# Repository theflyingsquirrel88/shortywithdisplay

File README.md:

# shortywithdisplay
PCB Design for the ShortywithDisplay Project

This Project is based on the design from kripton2035 from eevblog.com
https://www.eevblog.com/forum/testgear/finding-short-on-motherboards-with-a-shorty-(with-display)/

I was fixing my laptop and thinking there is a short somewhere which is hard to pin point. I then came across this project shorty with display and am very imppressed by it. I saw everyone was soldering component onto breadbroad but no PCB was ever designed for this. I then decided to take some time to design a PCB for this so that everyone will have a easier live down the road.
This PCB is designed with KiCAD 9.0. I used mostly 0603 SMD with some through hold components. You may Thesewant to take a look at the original Project to get an idea of what this PCB is for.

These days, you can order PCB online for a really low price. This make DIY project much easier.

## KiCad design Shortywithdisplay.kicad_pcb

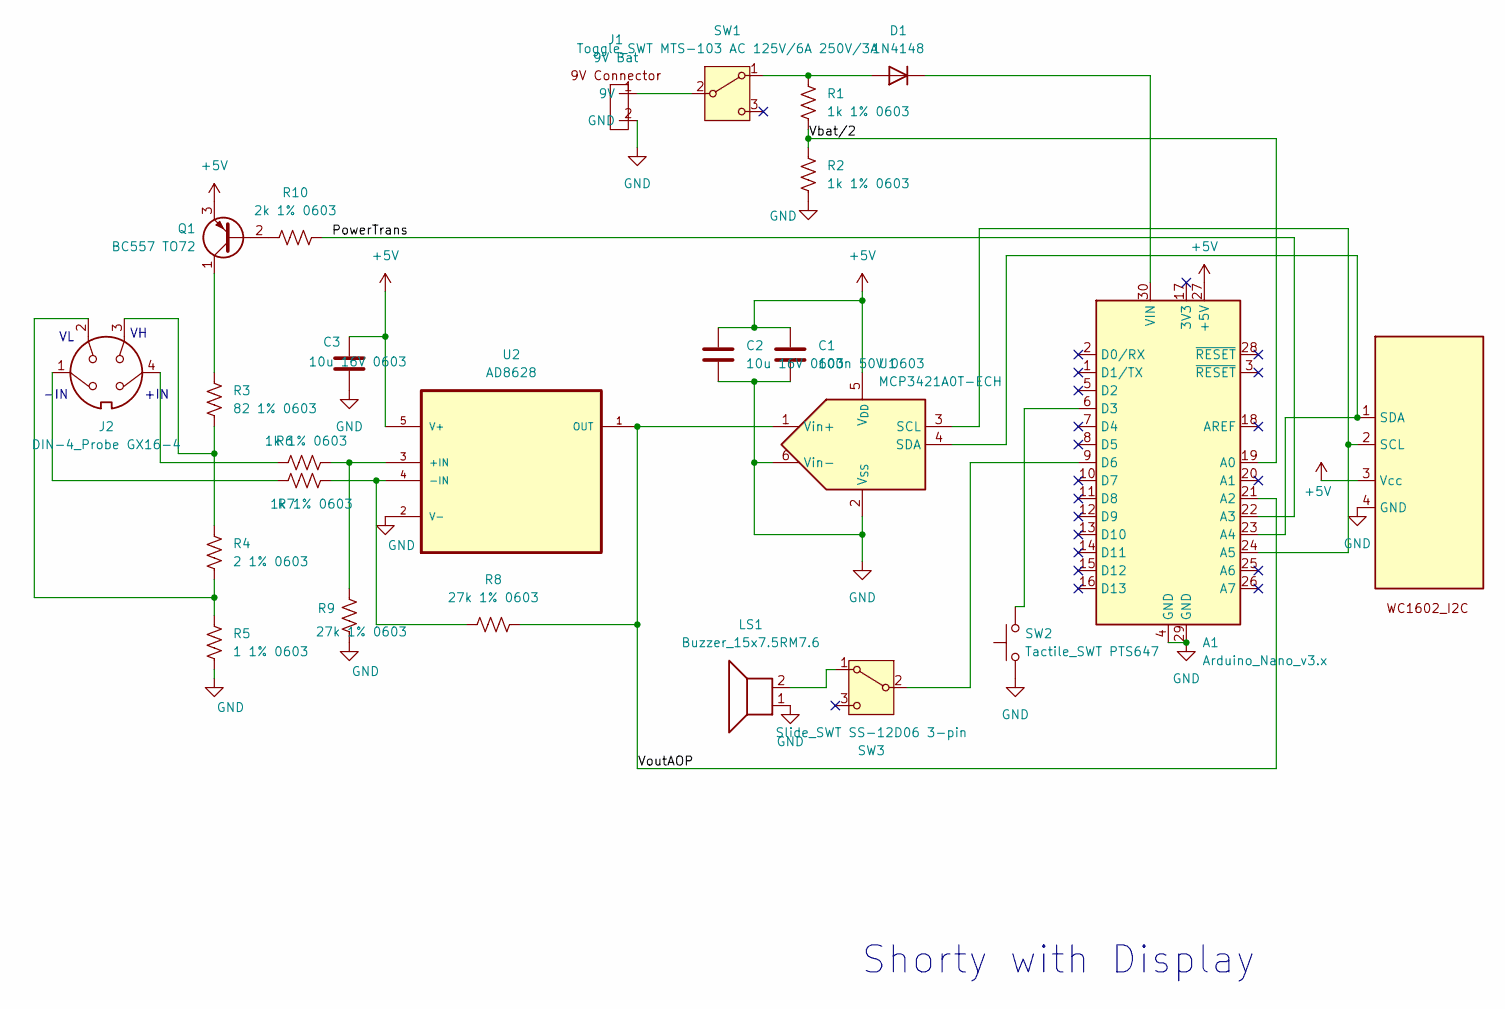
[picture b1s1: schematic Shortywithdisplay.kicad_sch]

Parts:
A1: Arduino_Nano_v3.x; Arduino_Nano_USB_nosilkscreen
C1: 100n 50V 0603; C_0603_1608Metric_Pad1.08x0.95mm_HandSolder
C2, C3: 10u 16V 0603; C_0603_1608Metric_Pad1.08x0.95mm_HandSolder
D1: 1N4148; D_DO-35_SOD27_P7.62mm_Horizontal
DS1: WC1602_I2C; WC1602A_I2C
J1: 9V Bat; PinSocket_1x02_P2.54mm_Vertical_NoModel
J2: DIN-4_Probe GX16-4; PinHeader_1x04_P2.54mm_Square
LS1: Buzzer_15x7.5RM7.6
Q1: BC557 TO72; TO-92_Inline
R1, R2, R6, R7: 1k 1% 0603; R_0603_1608Metric_Pad0.98x0.95mm_HandSolder
R3: 82 1% 0603; R_0603_1608Metric_Pad0.98x0.95mm_HandSolder
R4: 2 1% 0603; R_0603_1608Metric_Pad0.98x0.95mm_HandSolder
R5: 1 1% 0603; R_0603_1608Metric_Pad0.98x0.95mm_HandSolder
R8, R9: 27k 1% 0603; R_0603_1608Metric_Pad0.98x0.95mm_HandSolder
R10: 2k 1% 0603; R_0603_1608Metric_Pad0.98x0.95mm_HandSolder
SW1: Toggle_SWT MTS-103 AC 125V/6A 250V/3A; SW_toggle_1x03_P2.54mm_Vertical
SW2: Tactile_SWT PTS647; SW_Push_1P1T_4.26
SW3: Slide_SWT SS-12D06 3-pin; SW_slide_1x03_P2.54mm_Vertical
U1: MCP3421A0T-ECH; SOT-23-6
U2: AD8628; SOT-23-5_HandSoldering; MPN AD8628WARTZ-RL

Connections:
+5V: A1.27 (+5V), C1.1, C2.1, C3.1, DS1.3 (Vcc), Q1.3 (E), U1.5 (V_{DD}), U2.5 (V+)
/PowerTrans: A1.22 (A3), R10.2
/Vbat/2: A1.19 (A0), R1.2, R2.1
/VoutAOP: A1.21 (A2), R8.2, U1.1 (Vin+), U2.1 (OUT)
GND: A1.4 (GND), A1.29 (GND), C1.2, C2.2, C3.2, DS1.4 (GND), J1.2 (GND), LS1.1, R2.2, R5.2, R9.2, SW2.1, U1.2 (V_{SS}), U1.6 (Vin-), U2.2 (V-)
unnamed: A1.23 (A4), DS1.1 (SDA), U1.4 (SDA)
unnamed: A1.24 (A5), DS1.2 (SCL), U1.3 (SCL)
unnamed: A1.6 (D3), SW2.2
unnamed: A1.9 (D6), SW3.2 (B)
unnamed: A1.30 (VIN), D1.1 (K)
unnamed: D1.2 (A), R1.1, SW1.1 (A)
unnamed: J1.1 (9V), SW1.2 (B)
unnamed: J2.1, R7.1
unnamed: J2.2, R4.2, R5.1
unnamed: J2.3, R3.2, R4.1
unnamed: J2.4, R6.1
unnamed: Q1.2 (B), R10.1
unnamed: Q1.1 (C), R3.1
unnamed: LS1.2, SW3.1 (A)
unnamed: R6.2, R9.1, U2.3 (+IN)
unnamed: R7.2, R8.1, U2.4 (-IN)

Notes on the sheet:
-IN
+IN
Shorty with Display

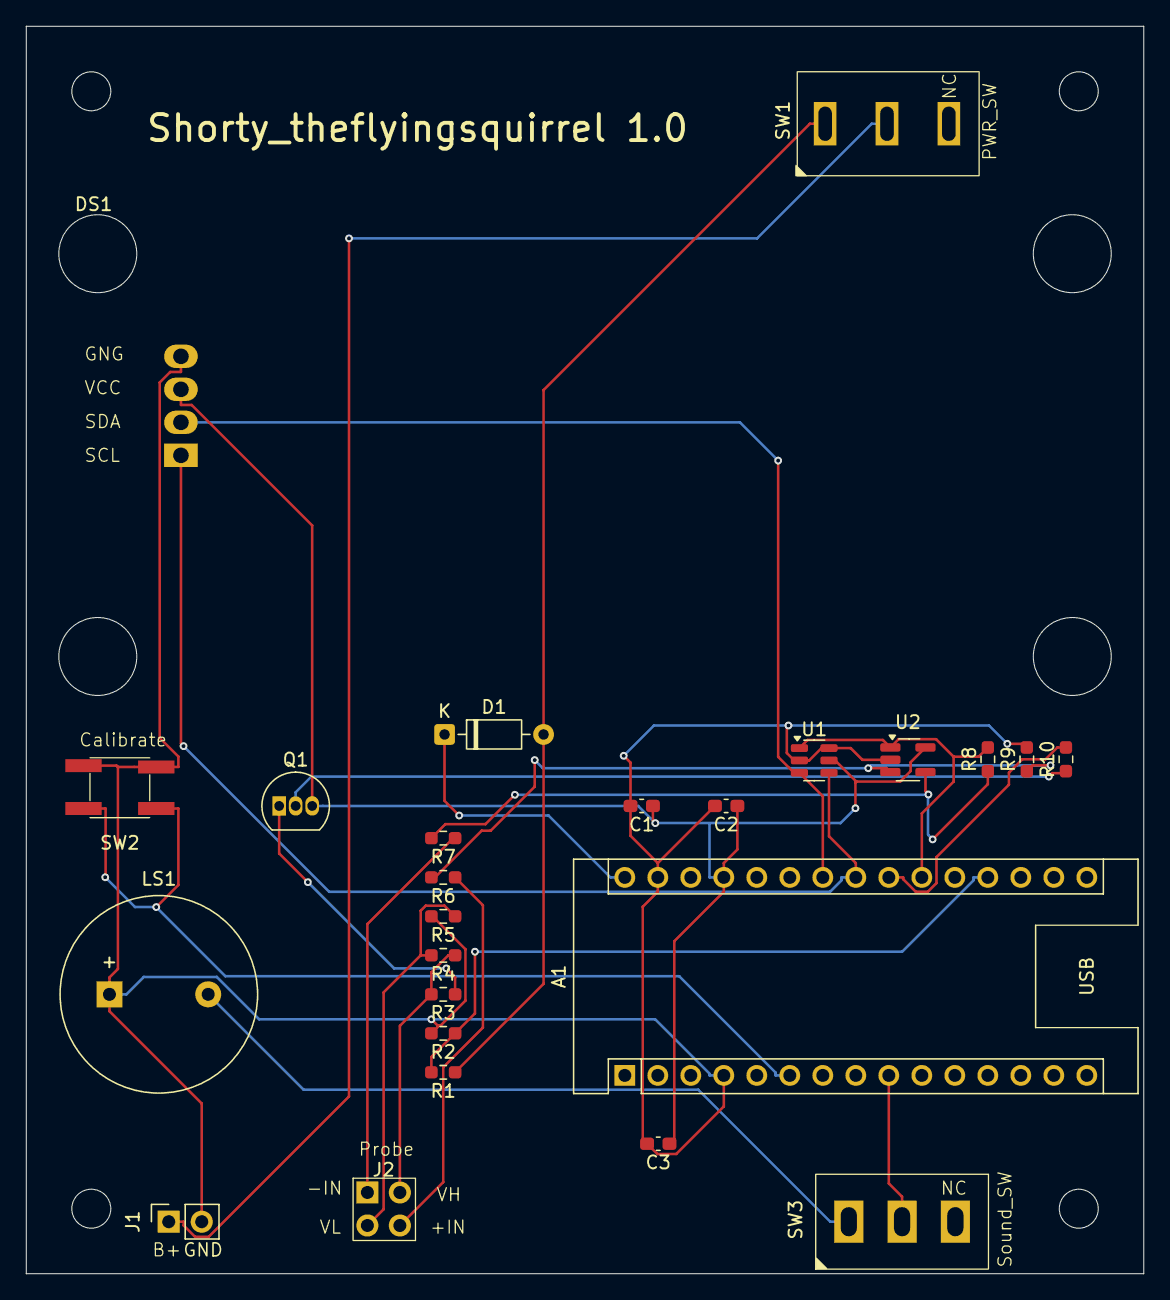
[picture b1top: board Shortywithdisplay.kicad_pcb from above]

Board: 2 copper layers, 86.0 x 96.0 mm, 25 parts (0 on the bottom side), 21 nets.

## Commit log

2025-06-25 Create test
2025-06-25 Create a
2025-06-27 Create LICENSE
